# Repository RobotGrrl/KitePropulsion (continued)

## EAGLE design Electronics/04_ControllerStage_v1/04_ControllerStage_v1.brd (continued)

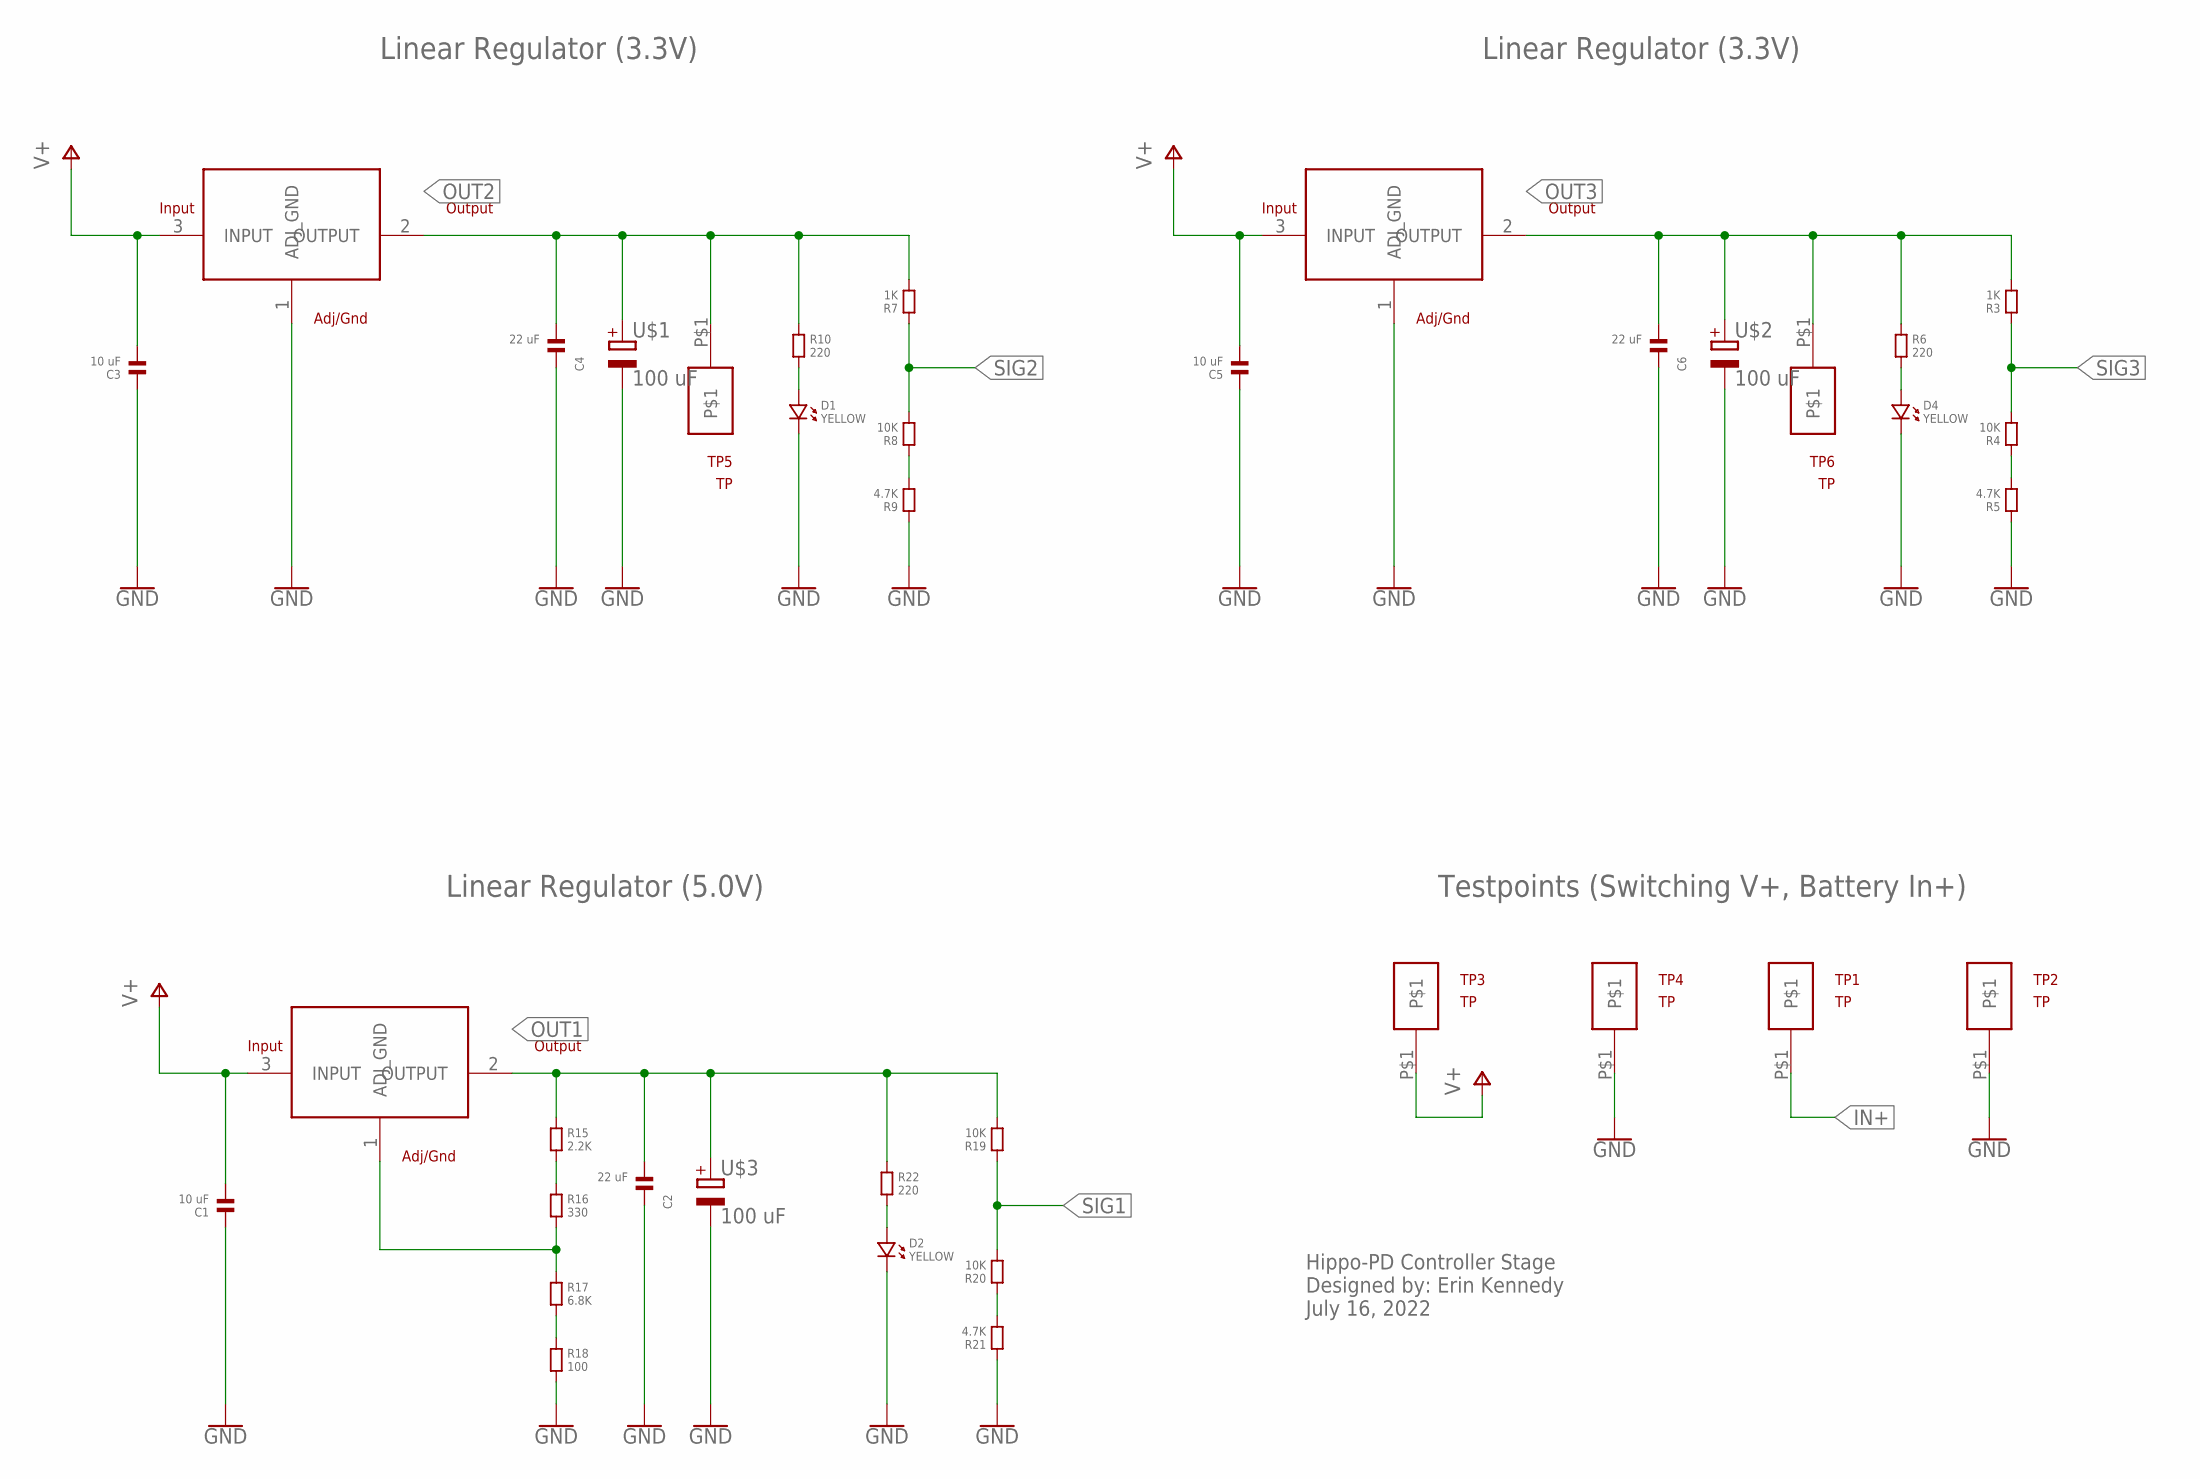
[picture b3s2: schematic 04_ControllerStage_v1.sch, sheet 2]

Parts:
C1, C3, C5: 10 uF; 1206
C2, C4, C6: 22 uF; 1206
D1, D2, D4: YELLOW; 1206.LED
R1, R2: AZ1117CDAZ1117CD; AZ1117CD
R3, R7: 1K; 1206
R4, R8, R19, R20: 10K; 1206
R5, R9, R21: 4.7K; 1206
R6, R10, R22: 220; 1206
R14: AZ1084C
R15: 2.2K; 1206
R16: 330; 1206
R17: 6.8K; 1206
R18: 100; 1206
TP1, TP2, TP3, TP4, TP5, TP6: TP
U$1, U$2, U$3: 100 uF; ELECTROLYTIC_CAP

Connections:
GND: C1.1, C2.1, C3.1, C4.1, C5.1, C6.1, D1.P$2 (2), D2.P$2 (2), D4.P$2 (2), R1.1 (ADJ_GND), R2.1 (ADJ_GND), R5.1, R9.1, R18.2, R21.1, TP2.P$1, TP4.P$1, U$1.-, U$2.-, U$3.-; also elsewhere on the board
IN+: TP1.P$1; also elsewhere on the board
unnamed: D1.P$1 (1), R10.2
unnamed: D4.P$1 (1), R6.2
unnamed: R4.1, R5.2
unnamed: R8.1, R9.2
unnamed: D2.P$1 (1), R22.2
unnamed: R15.2, R16.1
unnamed: R14.1 (ADJ_GND), R16.2, R17.1
unnamed: R17.2, R18.1
unnamed: R20.1, R21.2
OUT1: C2.2, R14.2 (OUTPUT), R15.1, R19.2, R22.1, U$3.+; also elsewhere on the board
OUT2: C4.2, R1.2 (OUTPUT), R7.2, R10.1, TP5.P$1, U$1.+; also elsewhere on the board
OUT3: C6.2, R2.2 (OUTPUT), R3.2, R6.1, TP6.P$1, U$2.+; also elsewhere on the board
SIG1: R19.1, R20.2; also elsewhere on the board
SIG2: R7.1, R8.2; also elsewhere on the board
SIG3: R3.1, R4.2; also elsewhere on the board
V+: C1.2, C3.2, C5.2, R1.3 (INPUT), R2.3 (INPUT), R14.3 (INPUT), TP3.P$1; also elsewhere on the board

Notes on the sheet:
Linear Regulator (5.0V)
Hippo-PD Controller Stage Designed by: Erin Kennedy July 16, 2022
Testpoints (Switching V+, Battery In+)
Linear Regulator (3.3V)

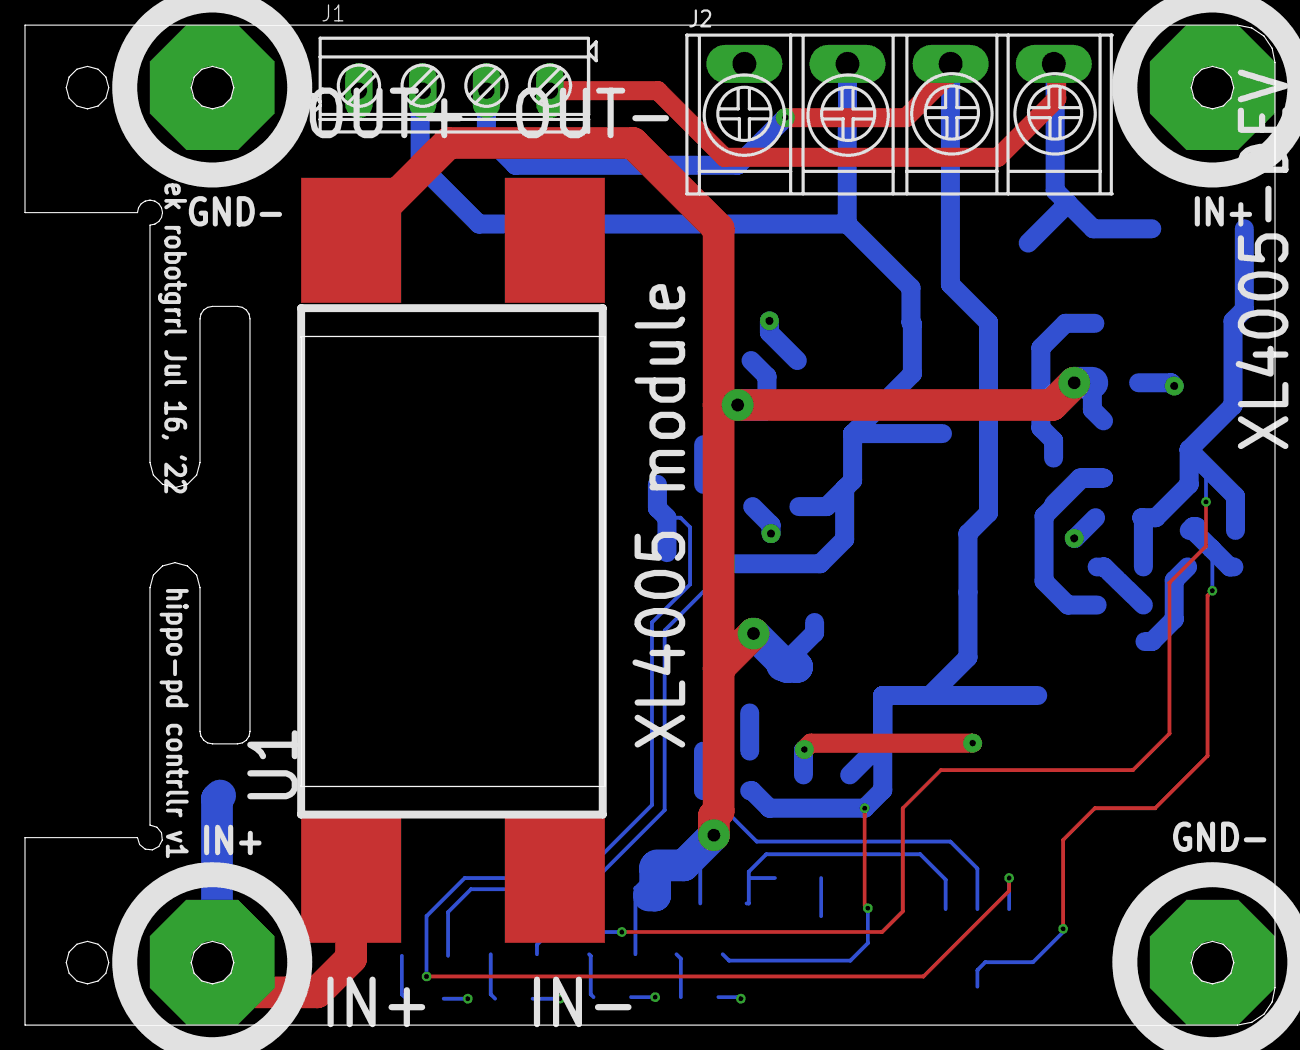
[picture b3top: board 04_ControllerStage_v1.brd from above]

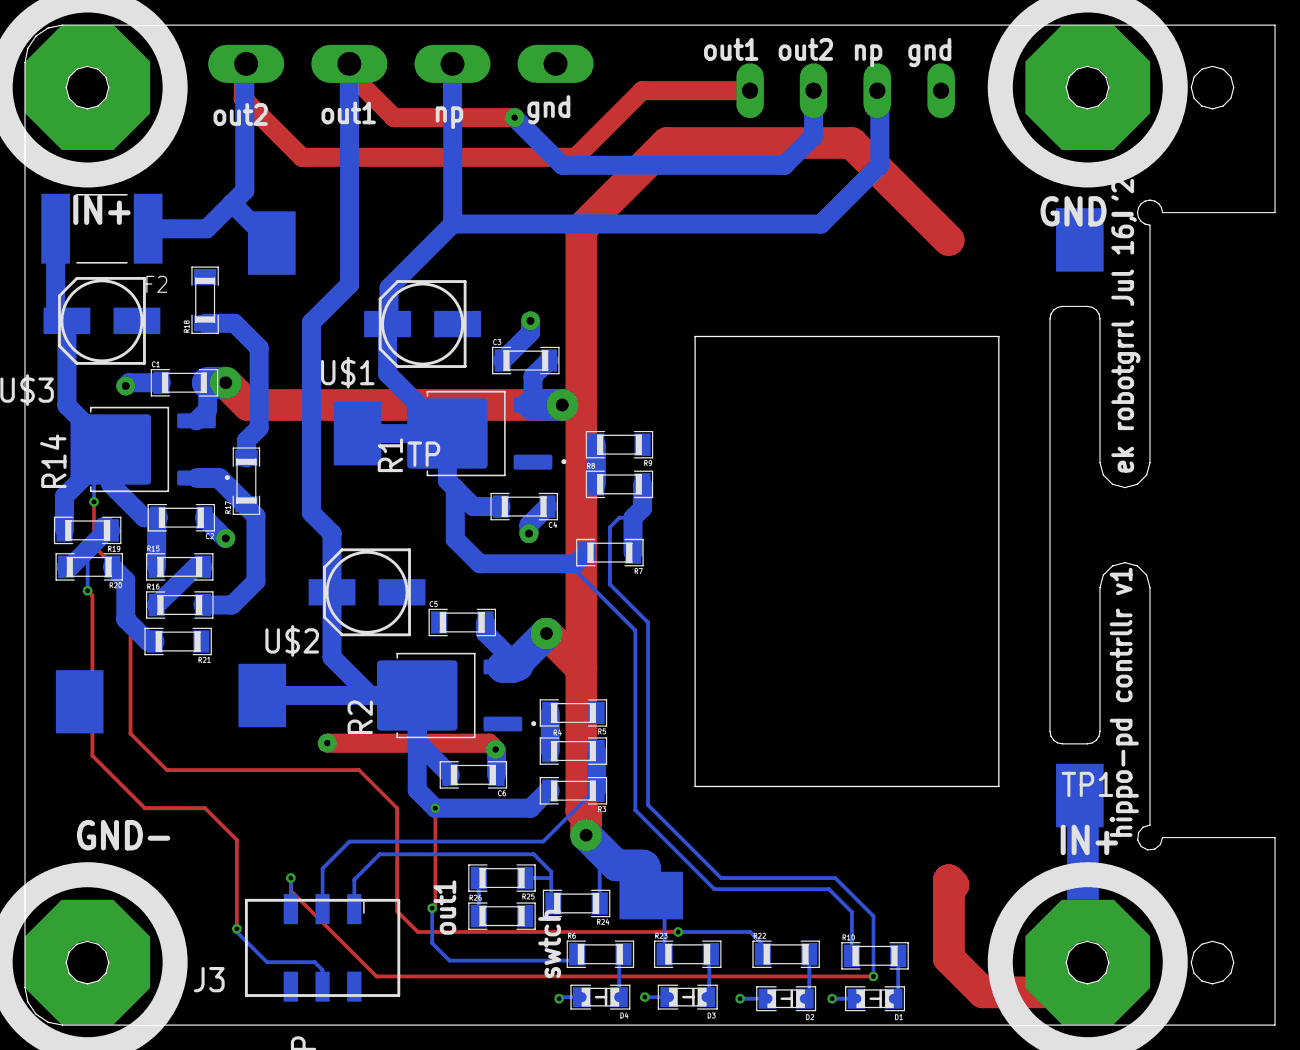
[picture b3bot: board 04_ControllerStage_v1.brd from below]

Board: 2 copper layers, 99.9 x 79.9 mm, 52 parts (45 on the bottom side), 22 nets.

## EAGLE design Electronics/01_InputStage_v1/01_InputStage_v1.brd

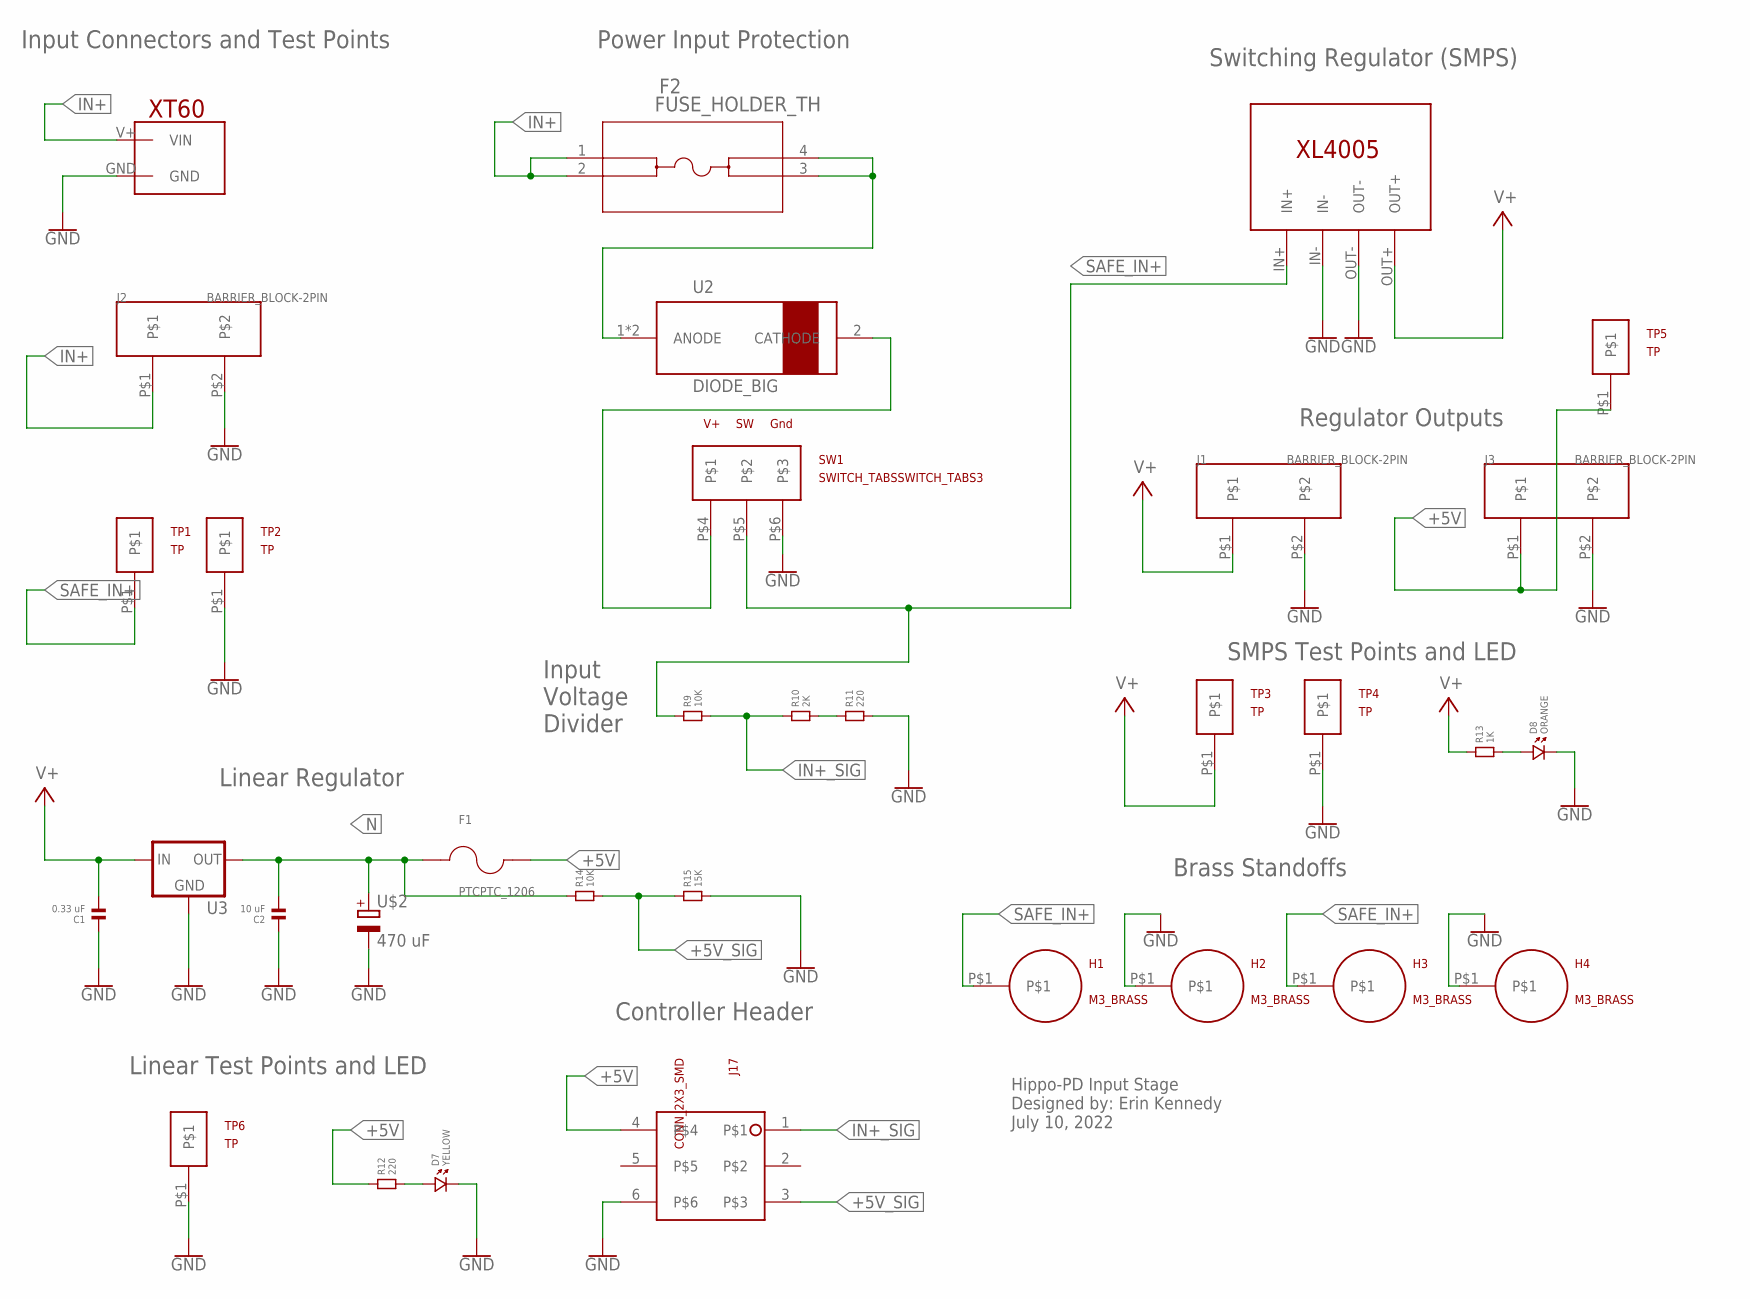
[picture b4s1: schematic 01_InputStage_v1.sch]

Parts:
C1: 0.33 uF; 1206
C2: 10 uF; 1206
D7: YELLOW; 1206.LED
D8: ORANGE; 1206.LED
F1: PTCPTC_1206; 1206
F2: FUSE_HOLDER_TH
H1, H2, H3, H4: M3_BRASS
J1, J2, J3: BARRIER_BLOCK-2PIN; BARRIERBLOCK-2PIN
J17: CONN_2X3_SMD; 2X3_SMD_CONNECTOR
R9, R14: 10K; 1206
R10: 2K; 1206
R11, R12: 220; 1206
R13: 1K; 1206
R15: 15K; 1206
SW1: SWITCH_TABSSWITCH_TABS3; SWITCH_TABS3
TP1, TP2, TP3, TP4, TP5, TP6: TP
U1: XL4005-DEV
U2: DIODE_BIG
U3: V_REG_78XXSINK; TO220-IGO
U$2: 470 uF; ELECTROLYTIC_CAP
U$5: XT60

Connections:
+5V: F1.2, J3.P$1, J17.4, R12.1, TP5.P$1
+5V_SIG: J17.3, R14.2, R15.1
GND: C1.1, C2.1, D7.P$2 (2), D8.P$2 (2), H2.P$1, H4.P$1, J1.P$2, J2.P$2, J3.P$2, J17.6, R11.2, R15.2, SW1.P$6, TP2.P$1, TP4.P$1, TP6.P$1, U1.IN-, U1.OUT-, U3.GND, U$2.-, U$5.GND
IN+: F2.1, F2.2, J2.P$1, U$5.V+ (VIN)
IN+_SIG: J17.1, R9.2, R10.1
N: C2.2, F1.1, R14.1, U3.OUT, U$2.+
unnamed: F2.3, F2.4, U2.1 (ANODE), U2.3 (ANODE)
unnamed: SW1.P$4, U2.2 (CATHODE)
unnamed: R10.2, R11.1
unnamed: D8.P$1 (1), R13.2
unnamed: D7.P$1 (1), R12.2
SAFE_IN+: H1.P$1, H3.P$1, R9.1, SW1.P$5, TP1.P$1, U1.IN+
V+: C1.2, J1.P$1, R13.1, TP3.P$1, U1.OUT+, U3.IN

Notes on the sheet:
Hippo-PD Input Stage Designed by: Erin Kennedy July 10, 2022
Brass Standoffs
Regulator Outputs
SMPS Test Points and LED
Switching Regulator (SMPS)
Power Input Protection
Input Voltage Divider
Linear Regulator
Controller Header
Linear Test Points and LED
Input Connectors and Test Points

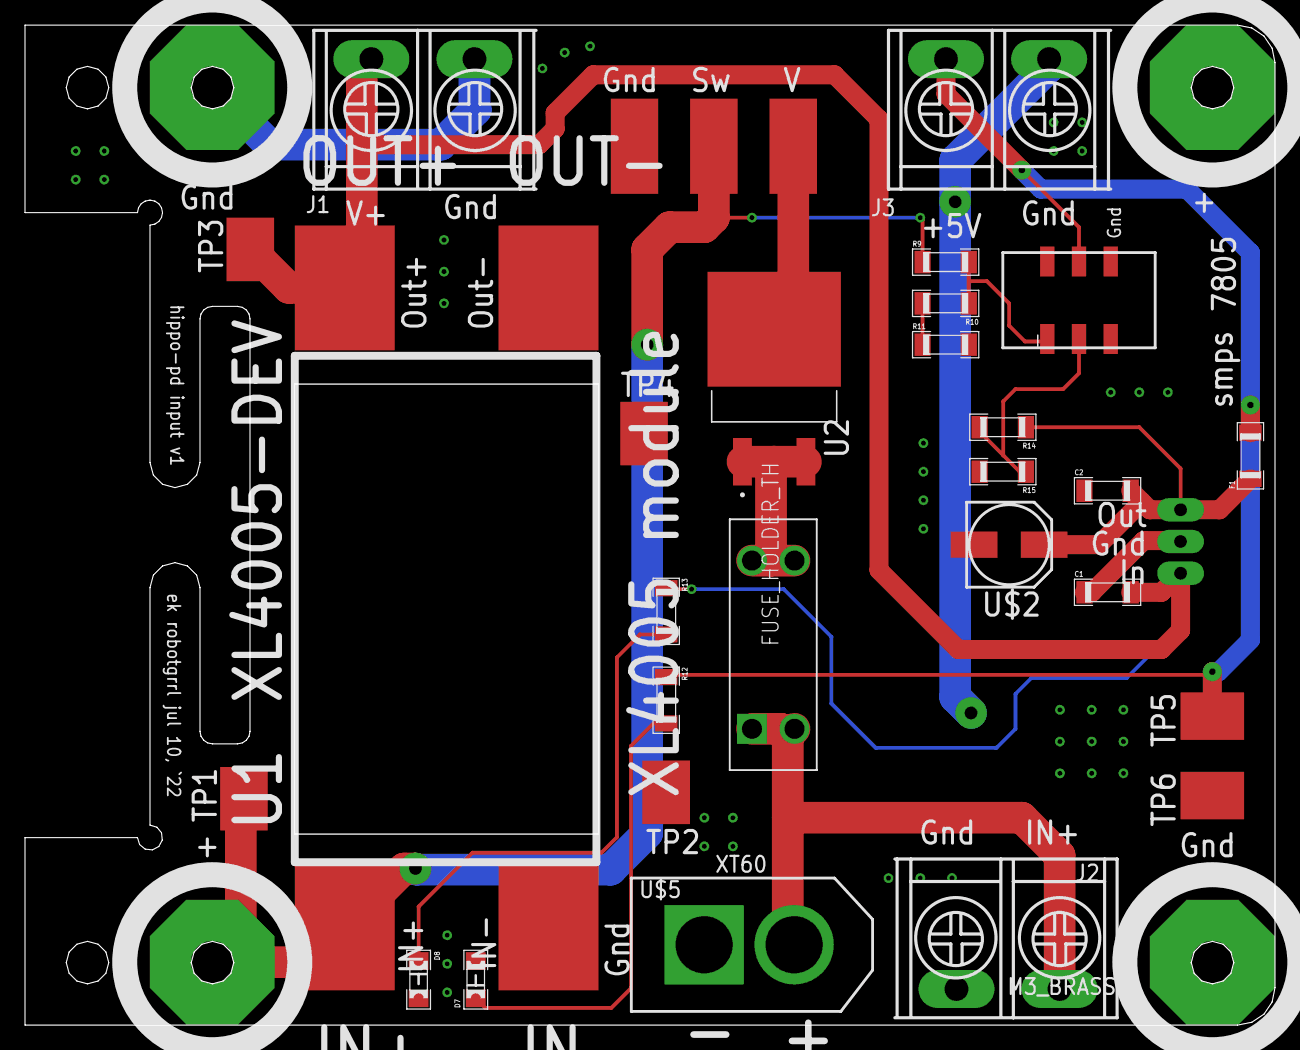
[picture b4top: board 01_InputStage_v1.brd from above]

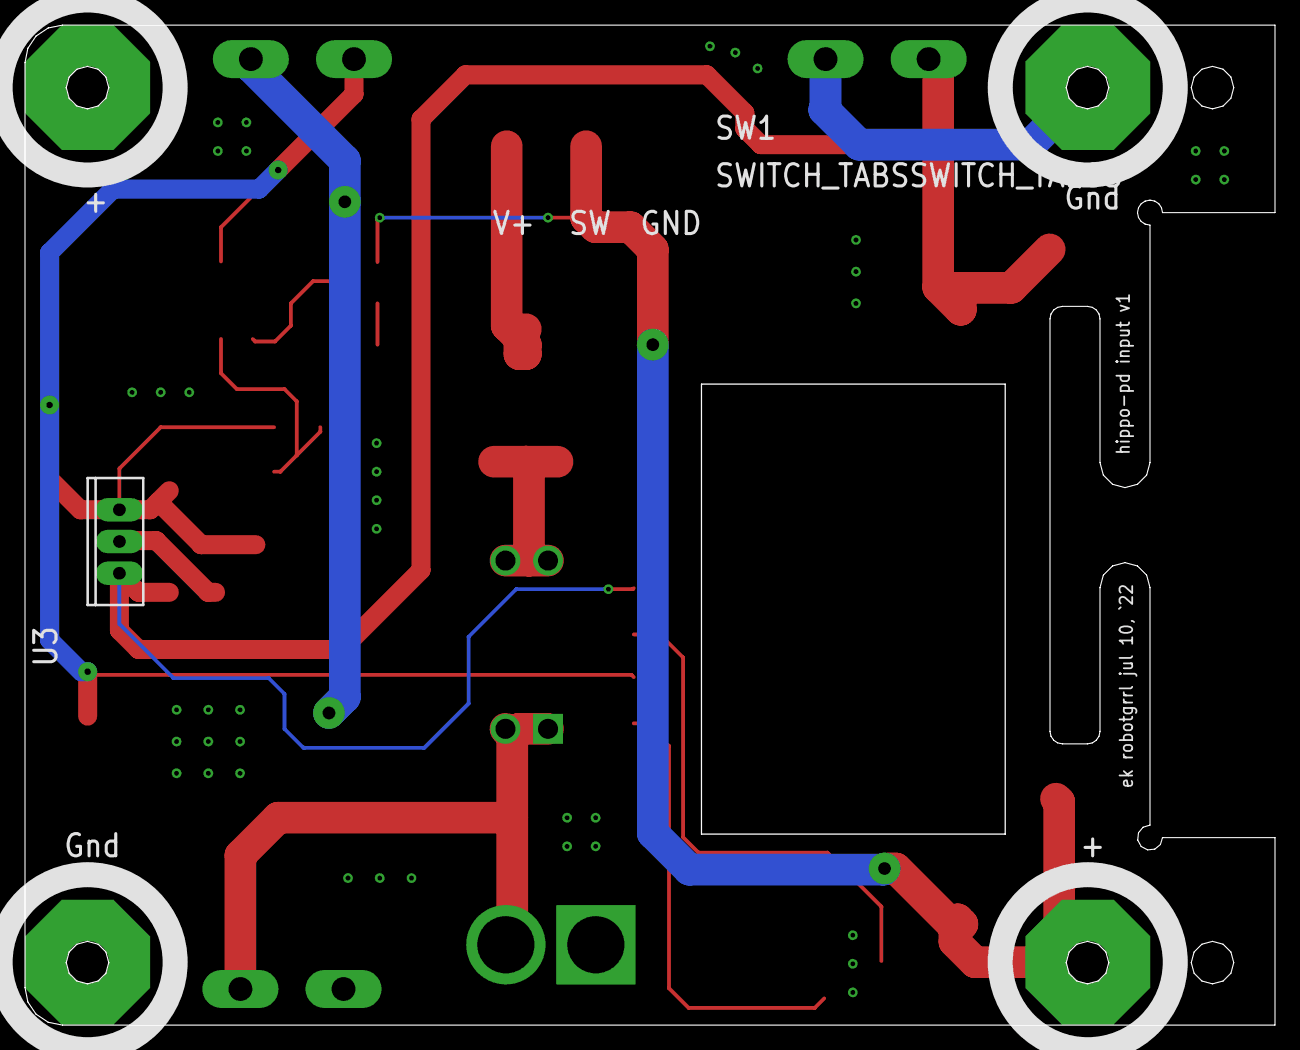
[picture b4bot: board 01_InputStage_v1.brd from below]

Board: 2 copper layers, 99.9 x 79.9 mm, 33 parts (2 on the bottom side), 13 nets.

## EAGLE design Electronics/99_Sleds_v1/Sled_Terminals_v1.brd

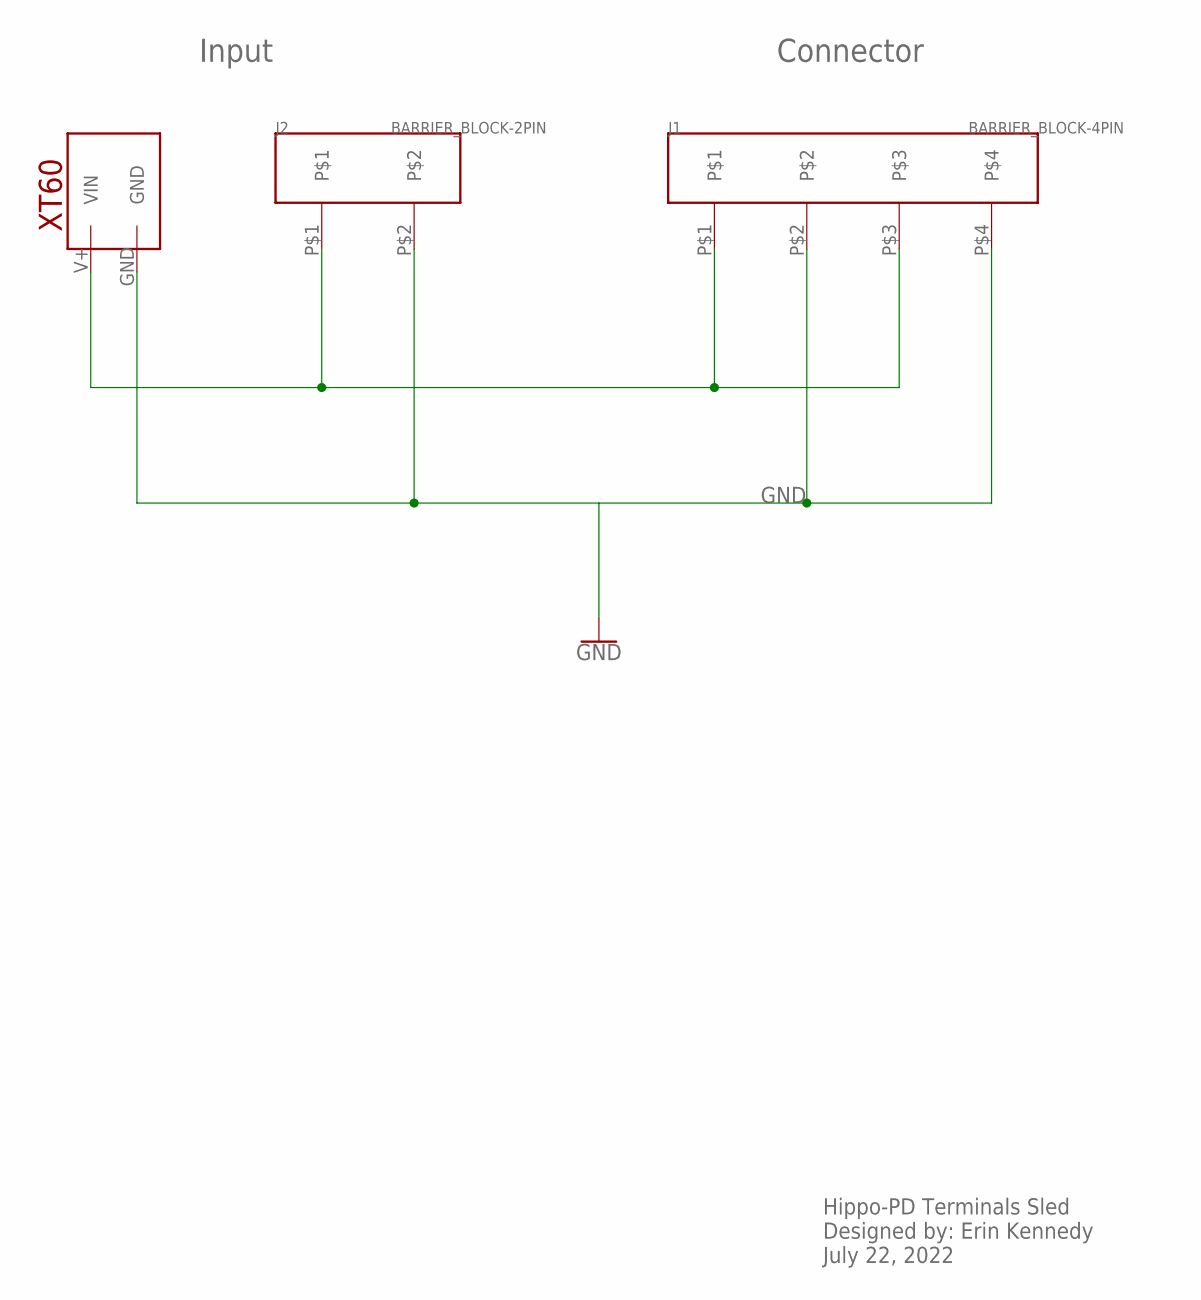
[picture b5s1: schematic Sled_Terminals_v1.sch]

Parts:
J1: BARRIER_BLOCK-4PIN; BARRIERBLOCK-4PIN
J2: BARRIER_BLOCK-2PIN; BARRIERBLOCK-2PIN
U$1: XT60

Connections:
GND: J1.P$2, J1.P$4, J2.P$2, U$1.GND
unnamed: J1.P$1, J1.P$3, J2.P$1, U$1.V+ (VIN)

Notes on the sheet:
Hippo-PD Terminals Sled Designed by: Erin Kennedy July 22, 2022
Connector
Input

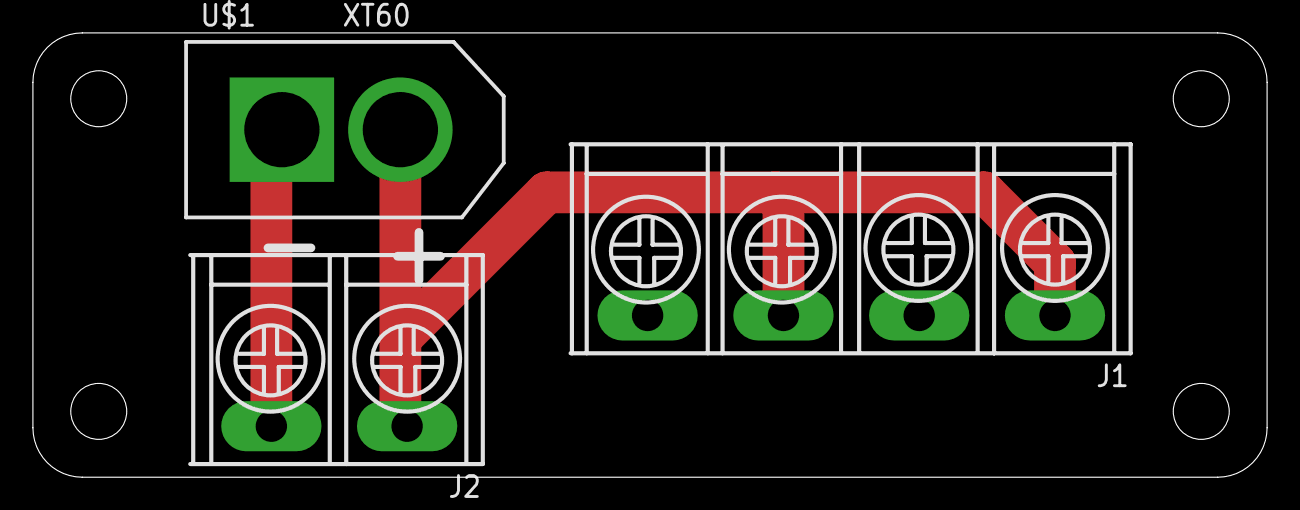
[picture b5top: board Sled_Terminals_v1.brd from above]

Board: 2 copper layers, 75.0 x 27.0 mm, 3 parts (0 on the bottom side), 2 nets.

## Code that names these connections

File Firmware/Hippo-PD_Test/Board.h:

#define LED_S03C        2
#define LED_S01         5
#define LED_S03         6
#define LED_S04         7
#define LED_S05         8
#define LED_S06         9
#define LED_S03D       10
#define BUZZER         11
#define FREE1          12
#define BUTTON1        24
#define BUTTON2        25
#define BUTTON3        26
#define FREE2          27
#define FREE3          28
#define LED_S03A       29
#define LED_S03B       30
#define 5V_SIG        A12
#define IN_SIG        A13
#define S03_SIG4      A14
#define S03_SIG3      A15
#define S03_SIG2      A16
#define S03_SIGSMPS   A17
#define S03_SIG1      A20
#define S06_SIG1      A21
#define S06_SIGSMPS   A22
#define LED            13
#define S04_SIG1       A0
#define S04_SIG2       A1
#define S04_SIG3       A2
#define S04_SIGSMPS    A3
#define S05_SIGNP      A6
#define S05_SIG2       A7
#define S05_SIG1       A8
#define S05_SIGSMPS    A9

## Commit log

2022-04-07 Processing sketch first commit
2022-04-08 Added controlP5 GUI, started on serial connection
2022-04-09 Fixed ports selector, fixed kite track percent, specified recording fps
2022-04-10 Added trace functionality, added actuator gui elements, fixed controlP5 rendering to video recording
2022-04-11 Simulate promulgate test, fixed buttons activating on start from controlP5, added actuator gui elements, refactored arduino to microcontroller
2022-04-11 Modified parser for double size messages. Commit before refactoring
2022-04-12 Refactored parsing (Promulgate) and moved code around
2022-04-13 Microcontroller code start
2022-04-14 Implemented video playback with computer vision
2022-04-15 Added logger to track x,y
2022-04-16 Filter trace with distance threshold and time
2022-04-18 Implemented input buffer on uart receive
2022-04-19 Added Promulgate and ported some of it, work in progress
2022-04-20 Improved logging with more parameters, hue track and kite trace enabled by default
2022-04-22 Added landscape draw mode
2022-04-23 .DS_Store banished!
2022-04-26 Generator design from yesterday
2022-04-26 Generator design prototype
2022-04-28 Ported command iterface code
2022-04-29 Created high level block diagram
2022-04-30 Added console command
2022-05-01 Updated design with guards and kite bearing tolerances
2022-05-01 Oscilloscope data from dc motor on generator
2022-05-01 Added motor mount
2022-05-03 Selected pins on board
2022-05-04 Setup pins and timer interrupt for stepper A
2022-05-06 Added BSP files?
2022-05-08 Landscape filter started
2022-05-09 Started draft of actuator driver
2022-05-09 Change pin to adapter pattern
2022-05-10 Setting pins on actuator instance, adjusting timer callback, added slp and endstop pins
2022-05-10 Updated pins to v1.1 to include SLP for each stepper. Improved labeling
2022-05-10 Attempts at implementing angled landscape filter - unsuccessful
2022-05-11 Fixed timer configuration, tested stepper motor with HAL
2022-05-12 Designed roll experiment model
2022-05-13 Still trying to fix landscape...
2022-05-13 Landscape line working - needs cleaning
2022-05-27 Created dowel experiment design
2022-05-30 Minor tidy up
2022-06-01 Servo control test code
2022-06-02 Added time of flight sensor project code - non-working
2022-06-03 Receiving values from sensor
2022-06-21 Designed pan mechanism
2022-06-22 Designed tilt mechanism
2022-06-23 Simulated basic model of wheel and kite
2022-07-05 Electronics Eagle library work in progress
2022-07-06 Additional electronic components to library
2022-07-06 Input stage with components placed, pre-routing
2022-07-07 Designed improved motor hub with 2 set screws for 4 mm axel
2022-07-07 Electronics library update
2022-07-08 Routed all 4 of the linear voltage regulators
2022-07-09 Completed routing of components on motor stage power supply board
2022-07-10 Motor stage circuit board v1 final
2022-07-11 Final electronics of input stage v1 board design
2022-07-12 Motor hub design improvements for build platform removal and surface area cooling on top layers
2022-07-13 Designed cover circuit board
2022-07-14 Added handle to cover stage circuit board
2022-07-14 Designed SBC stage circuit board
2022-07-15 Electronics servo stage work in progress
2022-07-16 Input stage: Added PTC and moved some traces around
2022-07-16 SBC stage: Moved test point to after the PTC fuse
2022-07-16 Servo stage: Completed routing
2022-07-17 Started controller stage electronics
2022-07-18 Components and values determined on schematic and routing started on controller stage
2022-07-19 Naming update to Hippo-PD
2022-07-19 Change fuse holder to through-hole component
2022-07-19 Finish routing controller stage electronics
2022-07-19 Cover stage artwork naming update
2022-07-20 Move LEDs to side on input stage
2022-07-20 Started monitor stage electronics
2022-07-21 Progress on monitor electronics schematic
2022-07-22 Routed monitor stage board
2022-07-22 Routing improvements on monitor stage electronics
2022-07-22 Board outlines and library update
2022-07-22 Designed helper boards
2022-07-22 Cover stage electronics v1 final
2022-07-22 Input stage electronics v1 final
2022-07-22 Monitor stage electronics v1 final
2022-07-22 Motor stage electronics v1 final
2022-07-22 Controller stage electronics v1 final
2022-07-22 Servo stage electronics v1 final
2022-07-22 SBC stage electronics v1 final
2022-07-24 Designed 3D printed pieces for Hippo-PD boards
2022-07-25 Revised Hippo-PD design based on fasteners
2022-07-26 Starting the test code for hippo-pd
2022-07-27 Calculation of efficiencies (power and thermal) for hippo-pd stage 01
2022-07-28 Efficiencies calculations for all stages in Hippo-PD
2022-07-29 Added signal struct outline start
2022-07-30 Minor change to start of signal code
2022-07-31 Designed test jig for 3D printing to hold hippo-pd stages in place
2022-08-01 Updated to use pointers
2022-08-02 Start of display test
2022-08-03 Updated refdes of some components
2022-08-04 Improvements to display test
2022-08-04 Created button debounce test
2022-08-05 Improvements to hippo-pd signal test
2022-08-05 Added led test for hippo-pd
2022-08-06 Citation file
2022-08-07 Started test point documentation
2022-08-08 Motor stage test points
2022-08-08 Physics model for Helium kite on Mars
2022-08-09 Idea concept of shield for Hippo-PD design
2022-08-10 Updated shell design on Hippo-PD
2022-08-11 Modifications to 3D print pieces for Hippo-PD assembly design based on the 20 mm brass hex standoffs used
2022-08-12 Improvements to 3D prints design for Hippo-PD (again)
2022-09-07 Designed line spool CAD model
2022-09-09 Animated CO2 jet particle system, with rover as a sprite, in Processing
